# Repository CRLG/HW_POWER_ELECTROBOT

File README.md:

# HW_POWER_ELECTROBOT
Carte électronique POWER_ELECTROBOT : schéma et routage

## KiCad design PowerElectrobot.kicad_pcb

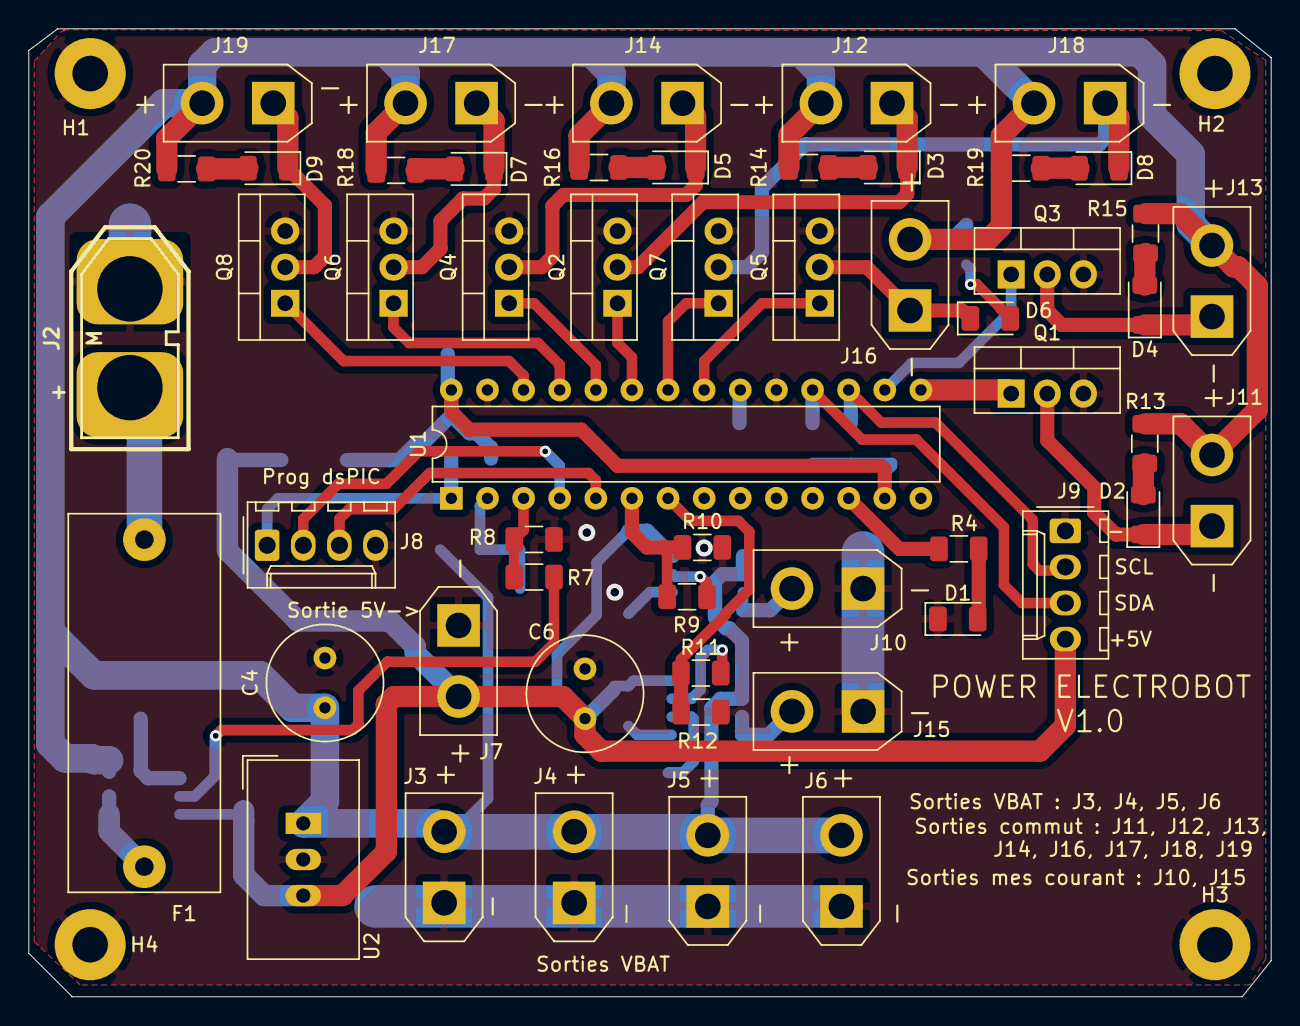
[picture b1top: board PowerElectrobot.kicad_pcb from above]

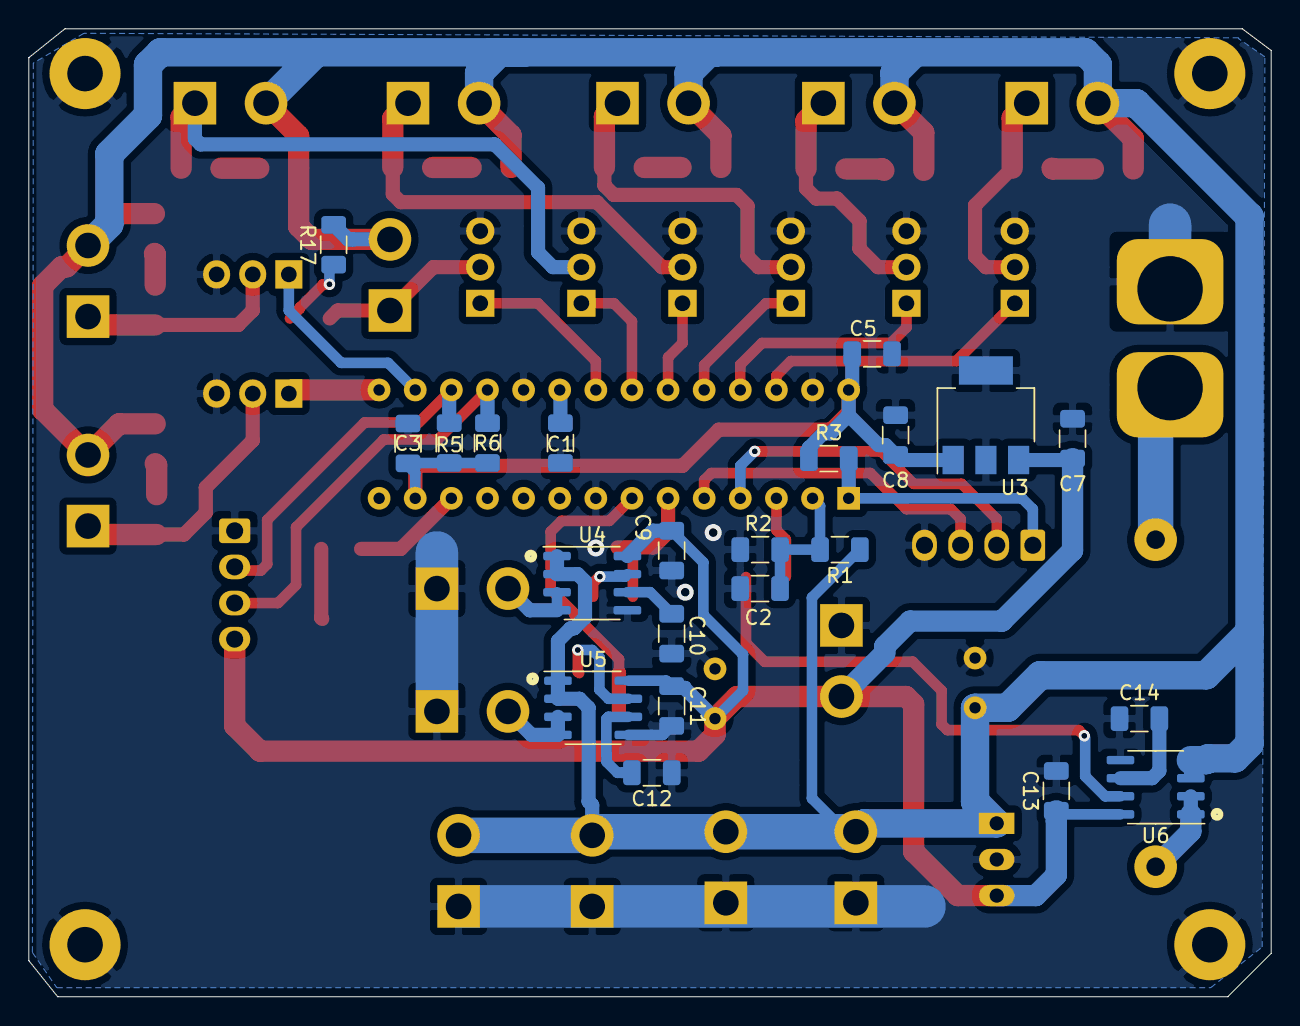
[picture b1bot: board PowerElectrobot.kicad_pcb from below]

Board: 2 copper layers, 87.4 x 68.1 mm, 80 parts (22 on the bottom side), 50 nets.

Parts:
C1: 10u; C_1206_3216Metric
C2, C3, C5, C9, C11, C13: 100n; C_1206_3216Metric
C4, C6: 220u; C_Radial_D8.0mm_H11.5mm_P3.50mm
C7: 1u; C_1206_3216Metric
C8: 47u; C_1206_3216Metric
C10, C12, C14: 1n; C_1206_3216Metric
D1, D2, D3, D4, D5, D6, D7, D8, D9: LED; LED_1206_3216Metric
F1: Fuse; Fuseholder_Schurter-5x20mm
H1, H2, H3, H4: MountingHole_Pad; MountingHole_2.5mm_Pad
J2: Conn_XT60M; XT60UPB-M
J3, J4, J5, J6, J7, J10, J11, J12, J13, J14, J15, J16, J17, J18, J19: Conn_XT30F; AMASS_XT30UPB-F_1x02_P5.0mm_Vertical
J8, J9: Conn_01x04; Molex_KK-254_AE-6410-04A_1x04_P2.54mm_Vertical
Q1, Q2, Q3, Q4, Q5, Q6, Q7, Q8: BTS117; TO-220-3_Vertical
R1, R8, R10, R12: 91k; R_1206_3216Metric
R2: 18k; R_1206_3216Metric
R3: 10k; R_1206_3216Metric
R4: 470; R_1206_3216Metric
R5, R6: 4.7k; R_1206_3216Metric
R7, R9, R11: 47k; R_1206_3216Metric
R13, R14, R15, R16, R17, R18, R19, R20: R; R_1206_3216Metric
U1: DSPIC33FJ128MC802-xSP; DIP-28_W7.62mm
U2: TSR_2-2450; Converter_DCDC_TRACO_TSR-2_THT
U3: MCP1804x-3302xDB; SOT-223-3_TabPin2
U4, U5: ACS712xLCTR-05B; SOIC-8_3.9x4.9mm_P1.27mm
U6: ACS712xLCTR-20A; SOIC-8_3.9x4.9mm_P1.27mm

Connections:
+5V: C6.1, C7.1, C9.1, C11.1, C13.1, J7.2, J9.4, U2.3, U3.3, U4.8, U5.8, U6.8
/3.3V_dsPIC: C3.1, C5.2, C8.1, R3.1, R5.2, R6.2, U1.13, U1.28, U3.1
/I2C_SCL1: J9.2, R5.1, U1.17
/I2C_SDA1: J9.3, R6.1, U1.18
/MEAS_CURR_1: R9.1, R10.1, U1.6
/MEAS_CURR_2: R11.1, R12.1, U1.7
/MEAS_CURR_VBAT: R7.1, R8.1, U1.3
/OUT_MEAS_1: J10.2, U4.3, U4.4
/OUT_MEAS_2: J15.2, U5.3, U5.4
/VBAT: C4.1, J3.2, J4.2, J5.2, J6.2, J11.2, J12.2, J13.2, J14.2, J16.2, J17.2, J18.2, J19.2, R1.1, R13.2, R14.2, R15.2, R16.2, R17.2, R18.2, R19.2, R20.2, U2.1, U4.1, U4.2, U5.1, U5.2, U6.3, U6.4
/VBAT_NP: F1.2, J2.2
/VBAT_P: F1.1, U6.1, U6.2
/VBAT_f: C2.1, R1.2, R2.1, U1.2
/dsPIC_MCLR: J8.1, R3.2, U1.1
/dsPIC_PGEC1: J8.3, U1.5
/dsPIC_PGED1: J8.2, U1.4
/dsPIC_Stor1: Q1.1, U1.15
/dsPIC_Stor2: Q3.1, U1.16
/dsPIC_Stor3: Q5.1, U1.21
/dsPIC_Stor4: Q7.1, U1.22
/dsPIC_Stor5: Q2.1, U1.23
/dsPIC_Stor6: Q4.1, U1.24
/dsPIC_Stor7: Q6.1, U1.25
/dsPIC_Stor8: Q8.1, U1.26
GND: C1.2, C2.2, C3.2, C4.2, C5.1, C6.2, C7.2, C8.2, C9.2, C10.1, C11.2, C12.1, C13.2, C14.1, D1.1, H1.1, H2.1, H3.1, H4.1, J2.1, J3.1, J4.1, J5.1, J6.1, J7.1, J8.4, J9.1, J10.1, J15.1, Q1.3, Q2.3, Q3.3, Q4.3, Q5.3, Q6.3, Q7.3, Q8.3, R2.2, R8.2, R10.2, R12.2, U1.8, U1.19, U1.27, U2.2, U3.2, U4.5, U5.5, U6.5
unnamed: C1.1, U1.20
unnamed: C10.2, U4.6
unnamed: C12.2, U5.6
unnamed: C14.2, U6.6
unnamed: D1.2, R4.1
unnamed: D2.1, J11.1, Q1.2
unnamed: D2.2, R13.1
unnamed: D3.1, J12.1, Q2.2
unnamed: D3.2, R14.1
unnamed: D4.1, J13.1, Q3.2
unnamed: D4.2, R15.1
unnamed: D5.1, J14.1, Q4.2
unnamed: D5.2, R16.1
unnamed: D6.1, J16.1, Q5.2
unnamed: D6.2, R17.1
unnamed: D7.1, J17.1, Q6.2
unnamed: D7.2, R18.1
unnamed: D8.1, J18.1, Q7.2
unnamed: D8.2, R19.1
unnamed: D9.1, J19.1, Q8.2
unnamed: D9.2, R20.1
unnamed: R4.2, U1.12
unnamed: R7.2, U6.7
unnamed: R9.2, U4.7
unnamed: R11.2, U5.7

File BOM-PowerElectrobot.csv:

Ref,Qnty,Value,Cmp name,Vendor,Footprint,Description,Vendor
"C1, ",1,10u,C,144-2510,Capacitor_SMD:C_1206_3216Metric,,
"C2, C9, C11, C3, C5, C13, ",6,100n,C,391-214,Capacitor_SMD:C_1206_3216Metric,,
"C4, C6, ",2,220u,CP,766-0066,Capacitor_THT:C_Radial_D8.0mm_H11.5mm_P3.50mm,,
"C7, ",1,1u,CP,903-8792,Capacitor_SMD:C_1206_3216Metric,,
"C8, ",1,47u,CP,916-2920,Capacitor_SMD:C_1206_3216Metric,,
"C10, C12, C14, ",3,1n,C,766-1116 ,Capacitor_SMD:C_1206_3216Metric,,
"D1, D2, D4, D6, D8, D3, D5, D7, D9, ",9,LED,LED,466-3908,LED_SMD:LED_1206_3216Metric,,
"F1, ",1,Fuse,Fuse,"176-9047
789-7808",Fuse:Fuseholder_Schurter-5x20mm,Fuse,
"H3, H1, H4, H2, ",4,MountingHole_Pad,MountingHole_Pad, –,MountingHole:MountingHole_2.5mm_Pad,Mounting Hole with connection,
"J2, ",1,Conn_XT60M,Conn_XT60M,180-5372,XT60:XT60UPB-M,,
"J7, J6, J5, J3, J4, J10, J15, J11, J13, J16, J18, J12, J14, J17, J19, ",15,Conn_XT30F,Conn_XT30F,Aliexpress,XT30:AMASS_XT30UPB-F_1x02_P5.0mm_Vertical,,
"J8, J9, ",2,Conn_01x04,Conn_01x04,,Connector_Molex:Molex_KK-254_AE-6410-04A_1x04_P2.54mm_Vertical,,
"Q1, Q3, Q5, Q7, Q2, Q4, Q6, Q8, ",8,BTS117,BTS117,110-7758,Package_TO_SOT_THT:TO-220-3_Vertical,Smart Low Side Power Switch,
"R1, R10, R12, R8, ",4,91k,R,866-2996,Resistor_SMD:R_1206_3216Metric,,
"R2, ",1,18k,R,679-1831,Resistor_SMD:R_1206_3216Metric,,
"R3, ",1,10k,R,125-1192,Resistor_SMD:R_1206_3216Metric,,
"R4, ",1,470,R,807-1246,Resistor_SMD:R_1206_3216Metric,,
"R6, R5, ",2,4.7k,R,125-1191,Resistor_SMD:R_1206_3216Metric,,
"R9, R11, R7, ",3,47k,R,807-1249,Resistor_SMD:R_1206_3216Metric,,
"R13, R15, R17, R19, R14, R16, R18, R20, ",8,R,R,,Resistor_SMD:R_1206_3216Metric,,
"U1, ",1,DSPIC33FJ128MC802-xSP,DSPIC33FJ128MC802-xSP,666-8362,Package_DIP:DIP-28_W7.62mm,,
"U2, ",1,TSR_2-2450,TSR_2-2450,906-8487,Convert_DCDC:Converter_DCDC_TRACO_TSR-2_THT,,
"U3, ",1,MCP1804x-3302xDB,MCP1804x-3302xDB,823-4396,Package_TO_SOT_SMD:SOT-223-3_TabPin2,,
"U4, U5, ",2,ACS712xLCTR-05B,ACS712xLCTR-05B,680-7131,Package_SO:SOIC-8_3.9x4.9mm_P1.27mm,"±5A Bidirectional Hall-Effect Current Sensor, +5.0V supply, 185mV/A, SOIC-8",
"U6, ",1,ACS712xLCTR-20A,ACS712xLCTR-20A,680-7135,Package_SO:SOIC-8_3.9x4.9mm_P1.27mm,"±20A Bidirectional Hall-Effect Current Sensor, +5.0V supply, 100mV/A, SOIC-8",

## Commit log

2019-06-23 Ajout de KICAD_LIB comme sous-module du projet
    KICAD_LIB est la librairie de composants et footprints CRLG pour KICAD
2019-07-24 Version initiale du projet
2019-07-27 Mise à jour schématique
2019-07-29 Mise à jour lib kicad
2019-07-30 Mise à jour KICAD_LIB
2019-07-30 Mise à jour schématique : condensateurs
2019-08-02 Mise à jour schématique (fusible, mesure courant VBAT)
    Suiteà discussion avec Alex
2019-08-02 Version initiale du PCB: placement des composants
2019-08-02 PCB : création des tailles de pistes
2019-08-03 Création des via de 1.2mm
2019-08-07 Début du routage de la carte
2019-08-07 mise a jour pcb
2019-09-01 Correction valeur de résistance LED à 470 Ohms
2019-09-02 Ajout d'une division de tension sur les entrées analogiques mesures de courant.
    Protection du dsPIC à 3.3V (entrées analogiques non tolérantes au 5V)
2019-09-02 Ajout des LEDs de debug sur les sorties pilotées
2019-09-02 Version initiale du placement de composants
2019-09-03 Version initiale du routage
2019-09-03 Ajout sérigraphie et dimensions
2019-09-15 Mise à jour empreinte XT60 + génération gerber
2019-09-15 Ajout des dimensions sur le PCB
2019-09-15 Fichiers gerber
2019-09-22 Ajout de la BOM : liste des composants<->Réfrences RS
2020-08-28 Mise à jour des modèles 3D des connecteurs XT30 et XT60
